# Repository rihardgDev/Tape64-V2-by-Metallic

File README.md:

# Tape64-V2-by-Metallic
Tape port to aux adaptor for Commodore 64, originally found: https://www.commodore.gen.tr/dosyalar/c64/Tape64v2_by_Metallic.pdf
And the design was shared through dropbox, to preserve it i have added it here.

.JPG)

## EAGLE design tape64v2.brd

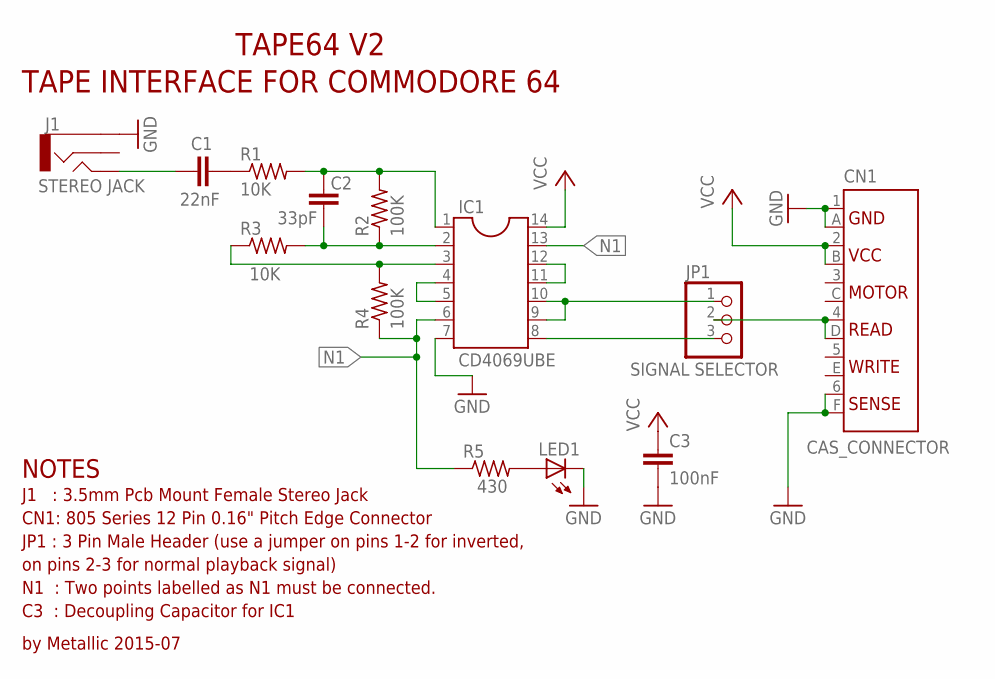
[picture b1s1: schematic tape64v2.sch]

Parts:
C1: 22nF; C050-025X075
C2: 33pF; C025-024X044
C3: 100nF; C050-035X075
CN1: CAS_CONNECTOR; CAS_CON
IC1: CD4069UBE; DIL14
J1: STEREO JACK; AUDIO-JACK
JP1: SIGNAL SELECTOR; 1X03
LED1: LED3MM
R1, R3: 10K; 0207/10
R2, R4: 100K; 0207/10
R5: 430; 0207/10

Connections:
GND: C3.2, CN1.1 (GND1), CN1.6 (SENSE1), CN1.A (GND2), CN1.F (SENSE2), IC1.7, J1.1, LED1.K (C)
N1: IC1.6, IC1.13, R4.1, R5.1
unnamed: IC1.3, R3.1, R4.2
unnamed: C1.1, J1.5
unnamed: C2.2, IC1.1, R1.2, R2.2
unnamed: IC1.4, IC1.5
unnamed: C2.1, IC1.2, R2.1, R3.2
unnamed: IC1.11, IC1.12
unnamed: IC1.9, IC1.10, JP1.1
unnamed: IC1.8, JP1.3
unnamed: CN1.4 (READ1), CN1.D (READ2), JP1.2
unnamed: LED1.A, R5.2
unnamed: C1.2, R1.1
VCC: C3.1, CN1.2 (VCC1), CN1.B (VCC2), IC1.14

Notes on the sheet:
J1 : 3.5mm Pcb Mount Female Stereo Jack
JP1 : 3 Pin Male Header (use a jumper on pins 1-2 for inverted,
CN1: 805 Series 12 Pin 0.16" Pitch Edge Connector
TAPE64 V2
on pins 2-3 for normal playback signal)
C3 : Decoupling Capacitor for IC1
NOTES
by Metallic 2015-07
N1 : Two points labelled as N1 must be connected.
TAPE INTERFACE FOR COMMODORE 64

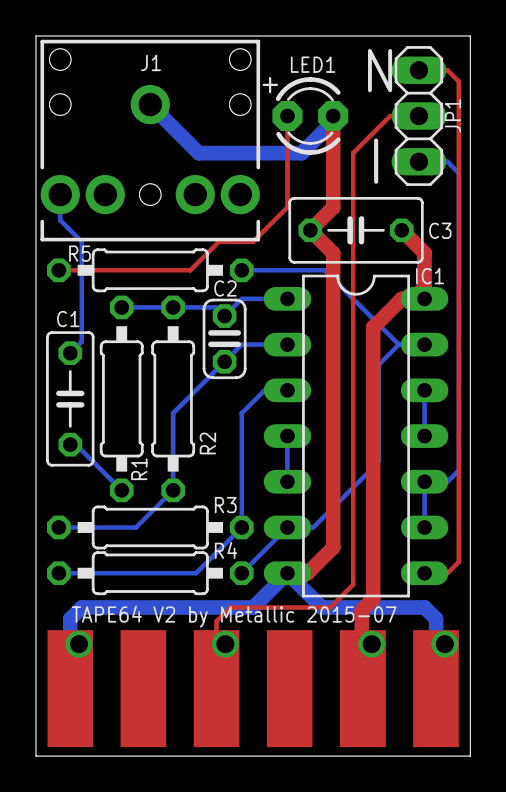
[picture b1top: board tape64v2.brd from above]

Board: 2 copper layers, 24.1 x 40.0 mm, 13 parts (0 on the bottom side), 14 nets.

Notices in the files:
parts and their libraries:
SparkFun: Licensing: CC v3.0 Share-Alike You are welcome to use this library for commercial purposes.
